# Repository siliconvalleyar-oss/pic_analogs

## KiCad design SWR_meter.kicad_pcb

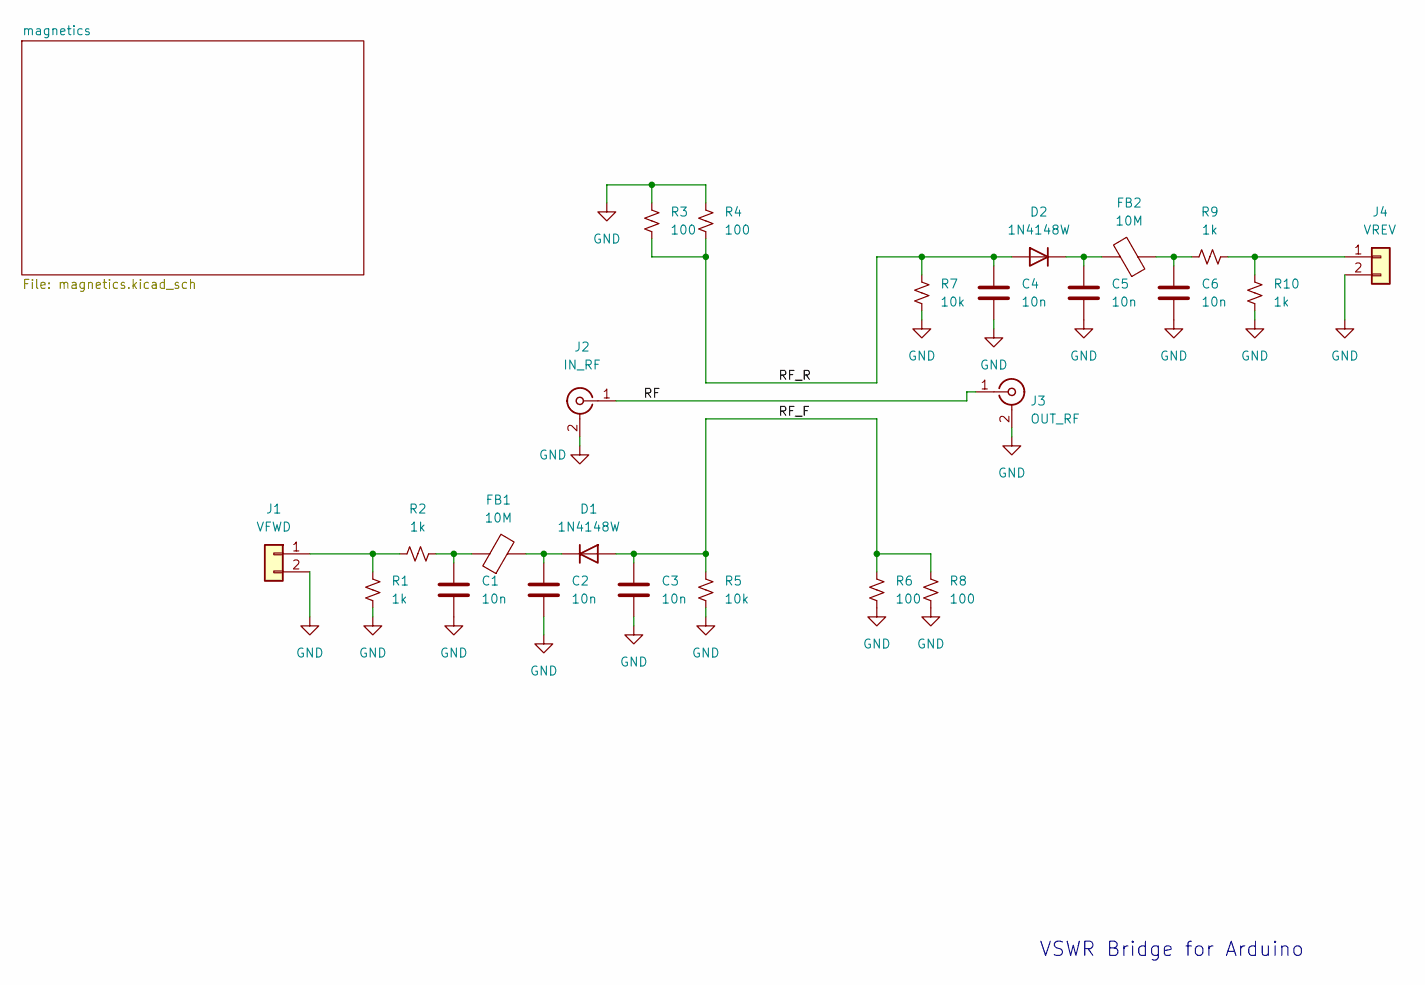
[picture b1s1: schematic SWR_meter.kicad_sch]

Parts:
C1, C2, C3, C4, C5, C6: 10n; C_0805_2012Metric
D1, D2: 1N4148W; D_SOD-123
FB1, FB2: 10M; L_1206_3216Metric
J1: VFWD; PinSocket_1x02_P2.54mm_Vertical
J2: IN_RF; SMA_Samtec_SMA-J-P-X-ST-EM1_EdgeMount
J3: OUT_RF; SMA_Samtec_SMA-J-P-X-ST-EM1_EdgeMount
J4: VREV; PinSocket_1x02_P2.54mm_Vertical
R1, R2, R9, R10: 1k; R_0805_2012Metric
R3, R4, R6, R8: 100; R_0805_2012Metric
R5, R7: 10k; R_0805_2012Metric

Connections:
/RF: J2.1 (In), J3.1 (In)
/RF_F: C3.1, D1.2 (A), R5.1, R6.1, R8.1
/RF_R: C4.1, D2.2 (A), R3.2, R4.2, R7.1
GND: C1.2, C2.2, C3.2, C4.2, C5.2, C6.2, J1.2, J2.2 (Ext), J3.2 (Ext), J4.2, R1.1, R3.1, R4.1, R5.2, R6.2, R7.2, R8.2, R10.1; also elsewhere on the board
unnamed: C1.1, FB1.1, R2.2
unnamed: C6.1, FB2.1, R9.1
unnamed: C2.1, D1.1 (K), FB1.2
unnamed: C5.1, D2.1 (K), FB2.2
unnamed: J1.1, R1.2, R2.1
unnamed: J4.1, R9.2, R10.2

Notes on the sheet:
VSWR Bridge for Arduino

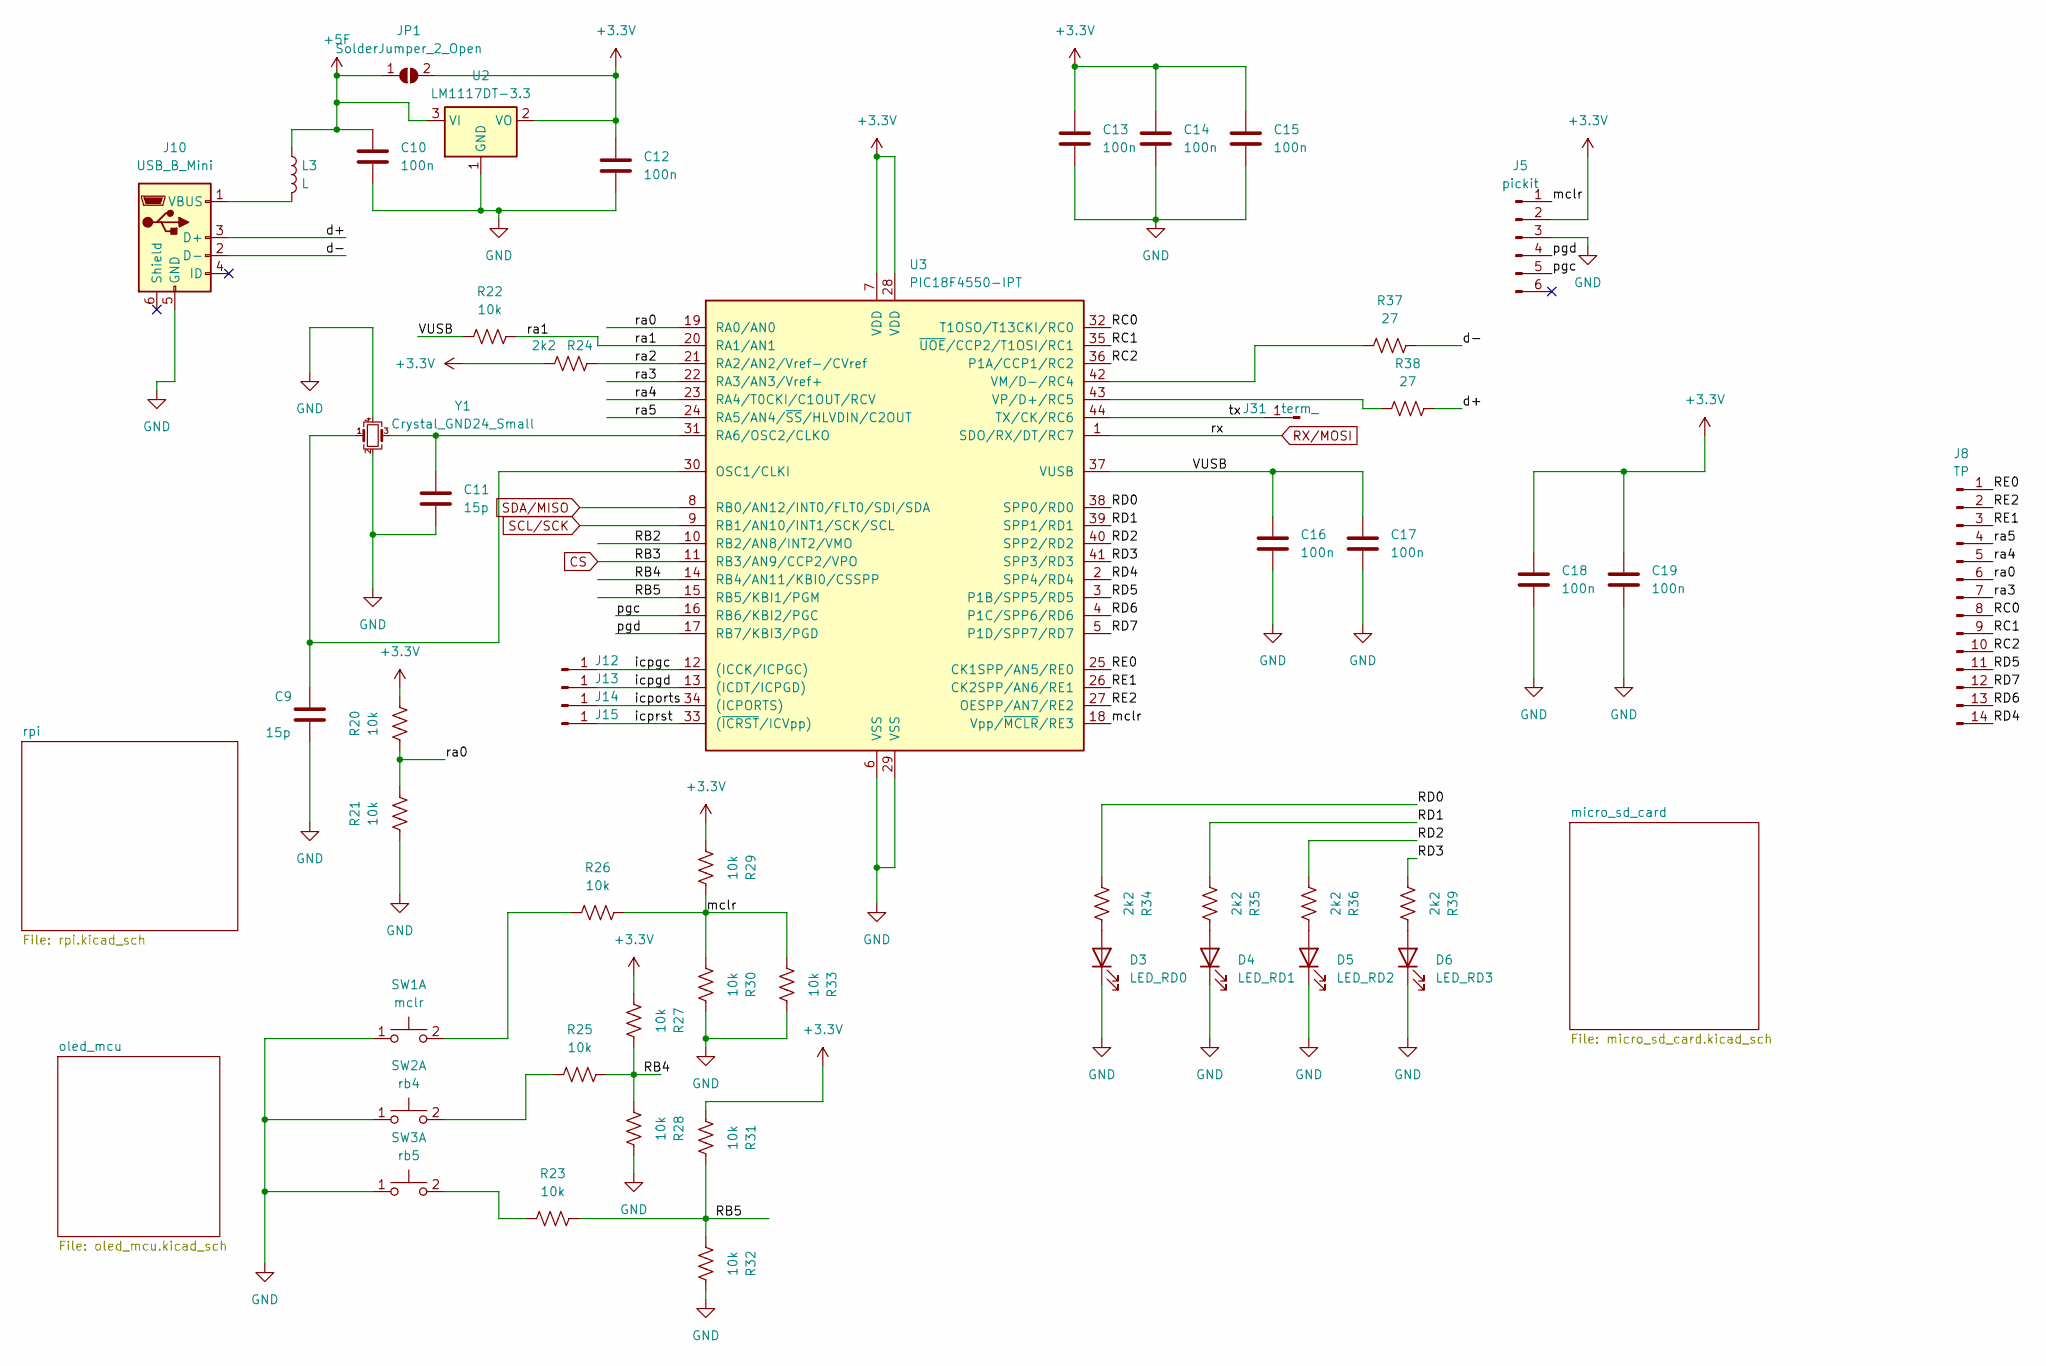
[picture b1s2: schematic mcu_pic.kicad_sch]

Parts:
C9, C11: 15p; C_0805_2012Metric
C10, C12: 100n; C_1206_3216Metric
C13, C14, C15, C16, C17, C18, C19: 100n; C_0603_1608Metric
D3: LED_RD0; D_0805_2012Metric
D4: LED_RD1; D_0805_2012Metric
D5: LED_RD2; D_0805_2012Metric
D6: LED_RD3; D_0805_2012Metric
J5: pickit; PinHeader_1x06_P2.54mm_Horizontal
J8: TP; PinHeader_2x08_P2.54mm_Vertical
J10: USB_B_Mini; USB_Mini-B_Wuerth_65100516121_Horizontal
J12, J13, J14, J15: connector_pin_smd_1mm
J31: term_; connector_pin_smd_1mm
JP1: SolderJumper_2_Open; SolderJumper-2_P1.3mm_Open_TrianglePad1.0x1.5mm
L3: L; L_Neosid_Ms42
R20, R21, R22, R23, R25, R26, R27, R28, R29, R30, R31, R32, R33: 10k; R_0603_1608Metric
R24, R34, R35, R36, R39: 2k2; R_0603_1608Metric
R37, R38: 27; R_0603_1608Metric
SW1: mclr; SW_Push_1P1T_NO_CK_KSC6xxJ
SW2: rb4; SW_Push_1P1T_NO_CK_KSC6xxJ
SW3: rb5; SW_Push_1P1T_NO_CK_KSC6xxJ
U2: LM1117DT-3.3; TO-252-3_TabPin2
U3: PIC18F4550-IPT; TQFP-44_10x10mm_P0.8mm
Y1: Crystal_GND24_Small; Oscillator_SMD_Abracon_ASE-4Pin_3.2x2.5mm

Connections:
+3.3V: C12.1, C13.1, C14.1, C15.1, C18.1, C19.1, J5.2, JP1.2 (B), R20.1, R24.2, R27.2, R29.2, R31.2, U2.2 (VO), U3.7 (VDD), U3.28 (VDD); also elsewhere on the board
+5F: C10.1, JP1.1 (A), L3.1, U2.3 (VI); also elsewhere on the board
/magnetics/mcu_pic/RB2: U3.10 (RB2/AN8/INT2/VMO)
/magnetics/mcu_pic/RB4: R25.1, R27.1, R28.2, U3.14 (RB4/AN11/KBI0/CSSPP)
/magnetics/mcu_pic/RB5: R23.1, R31.1, R32.2, U3.15 (RB5/KBI1/PGM)
/magnetics/mcu_pic/RC0: J8.8, U3.32 (T1OSO/T13CKI/RC0)
/magnetics/mcu_pic/RC1: J8.9, U3.35 (~UOE/CCP2/T1OSI/RC1)
/magnetics/mcu_pic/RC2: J8.10, U3.36 (P1A/CCP1/RC2)
/magnetics/mcu_pic/RD0: R34.2, U3.38 (SPP0/RD0)
/magnetics/mcu_pic/RD1: R35.2, U3.39 (SPP1/RD1)
/magnetics/mcu_pic/RD2: R36.2, U3.40 (SPP2/RD2)
/magnetics/mcu_pic/RD3: R39.2, U3.41 (SPP3/RD3)
/magnetics/mcu_pic/RD4: J8.14, U3.2 (SPP4/RD4)
/magnetics/mcu_pic/RD5: J8.11, U3.3 (P1B/SPP5/RD5)
/magnetics/mcu_pic/RD6: J8.13, U3.4 (P1C/SPP6/RD6)
/magnetics/mcu_pic/RD7: J8.12, U3.5 (P1D/SPP7/RD7)
/magnetics/mcu_pic/RE0: J8.1, U3.25 (CK1SPP/AN5/RE0)
/magnetics/mcu_pic/RE1: J8.3, U3.26 (CK2SPP/AN6/RE1)
/magnetics/mcu_pic/RE2: J8.2, U3.27 (OESPP/AN7/RE2)
/magnetics/mcu_pic/VUSB: C16.1, C17.1, R22.2, U3.37 (VUSB)
/magnetics/mcu_pic/d+: J10.3 (D+), R38.1
/magnetics/mcu_pic/d-: J10.2 (D-), R37.1
/magnetics/mcu_pic/icpgc: J12.1 (Pin_1_1), U3.12 ((ICCK/ICPGC))
/magnetics/mcu_pic/icpgd: J13.1 (Pin_1_1), U3.13 ((ICDT/ICPGD))
/magnetics/mcu_pic/icports: J14.1 (Pin_1_1), U3.34 ((ICPORTS))
/magnetics/mcu_pic/icprst: J15.1 (Pin_1_1), U3.33 ((~ICRST/ICVpp))
/magnetics/mcu_pic/mclr: J5.1, R26.1, R29.1, R30.2, R33.2, U3.18 (Vpp/~MCLR/RE3)
/magnetics/mcu_pic/pgc: J5.5, U3.16 (RB6/KBI2/PGC)
/magnetics/mcu_pic/pgd: J5.4, U3.17 (RB7/KBI3/PGD)
/magnetics/mcu_pic/ra0: J8.6, R20.2, R21.1, U3.19 (RA0/AN0)
/magnetics/mcu_pic/ra1: R22.1, U3.20 (RA1/AN1)
/magnetics/mcu_pic/ra2: R24.1, U3.21 (RA2/AN2/Vref-/CVref)
/magnetics/mcu_pic/ra3: J8.7, U3.22 (RA3/AN3/Vref+)
/magnetics/mcu_pic/ra4: J8.5, U3.23 (RA4/T0CKI/C1OUT/RCV)
/magnetics/mcu_pic/ra5: J8.4, U3.24 (RA5/AN4/~SS/HLVDIN/C2OUT)
/magnetics/mcu_pic/tx: J31.1 (Pin_1_1), U3.44 (TX/CK/RC6)
CS: U3.11 (RB3/AN9/CCP2/VPO); also elsewhere on the board
GND: C9.2, C10.2, C11.2, C12.2, C13.2, C14.2, C15.2, C16.2, C17.2, C18.2, C19.2, D3.1 (K), D4.1 (K), D5.1 (K), D6.1 (K), J5.3, J10.5 (GND), J10.6 (Shield), R21.2, R28.1, R30.1, R32.1, R33.1, SW1.1 (C), SW2.1 (C), SW3.1 (C), U2.1 (GND), U3.6 (VSS), U3.29 (VSS), Y1.2, Y1.4; also elsewhere on the board
unnamed: D3.2 (A), R34.1
unnamed: D4.2 (A), R35.1
unnamed: D5.2 (A), R36.1
unnamed: D6.2 (A), R39.1
unnamed: J10.1 (VBUS), L3.2
unnamed: R26.2, SW1.2 (D)
unnamed: R25.2, SW2.2 (D)
unnamed: R23.2, SW3.2 (D)
unnamed: C9.1, U3.30 (OSC1/CLKI), Y1.1
unnamed: C11.1, U3.31 (RA6/OSC2/CLKO), Y1.3
unnamed: R37.2, U3.42 (VM/D-/RC4)
unnamed: R38.2, U3.43 (VP/D+/RC5)
RX/MOSI: U3.1 (SDO/RX/DT/RC7); also elsewhere on the board
SCL/SCK: U3.9 (RB1/AN10/INT1/SCK/SCL); also elsewhere on the board
SDA/MISO: U3.8 (RB0/AN12/INT0/FLT0/SDI/SDA); also elsewhere on the board

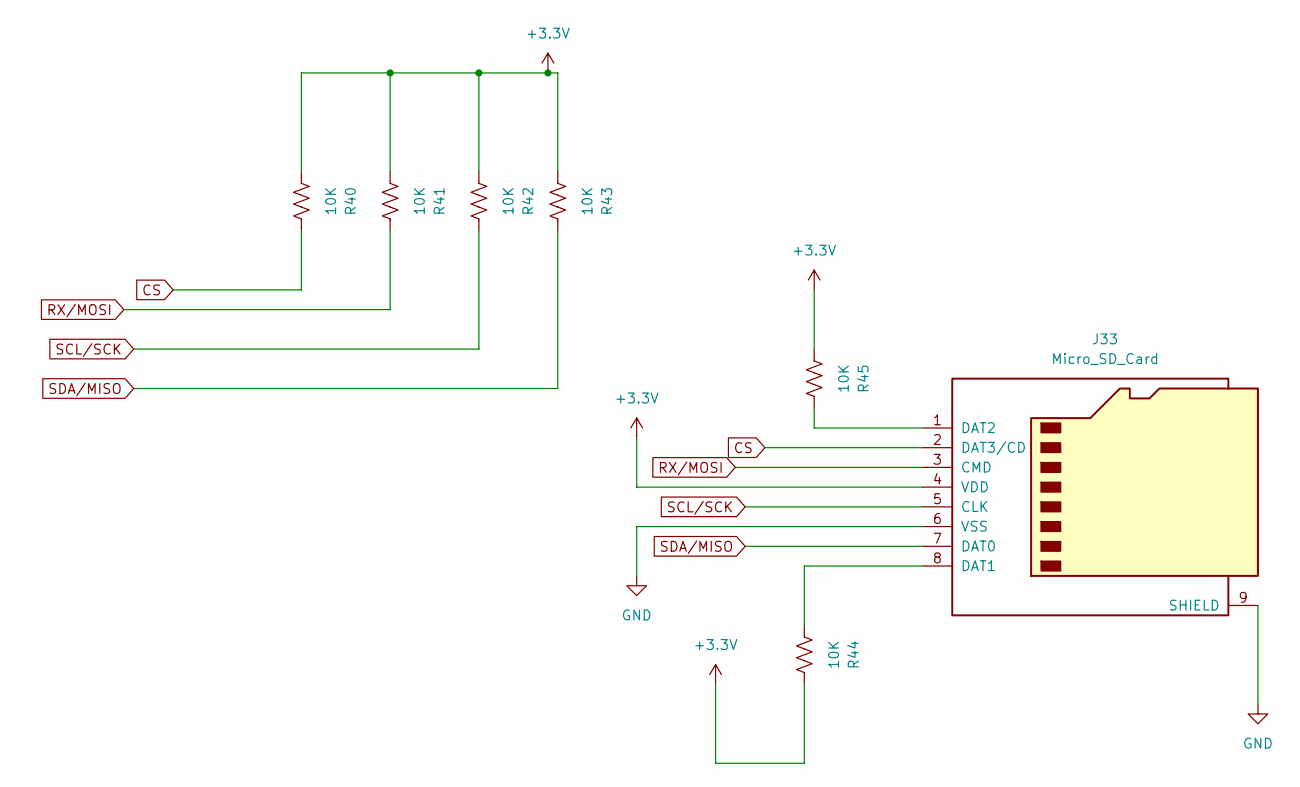
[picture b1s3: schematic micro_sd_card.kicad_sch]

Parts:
J33: Micro_SD_Card; 3M_2908-05WB-MG
R40, R41, R42, R43, R44, R45: 10K; R_0603_1608Metric

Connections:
+3.3V: J33.4 (VDD), R40.2, R41.2, R42.2, R43.2, R44.1, R45.2; also elsewhere on the board
CS: J33.2 (DAT3/CD), R40.1; also elsewhere on the board
GND: J33.6 (VSS), J33.9 (SHIELD); also elsewhere on the board
unnamed: J33.8 (DAT1), R44.2
unnamed: J33.1 (DAT2), R45.1
RX/MOSI: J33.3 (CMD), R41.1; also elsewhere on the board
SCL/SCK: J33.5 (CLK), R42.1; also elsewhere on the board
SDA/MISO: J33.7 (DAT0), R43.1; also elsewhere on the board

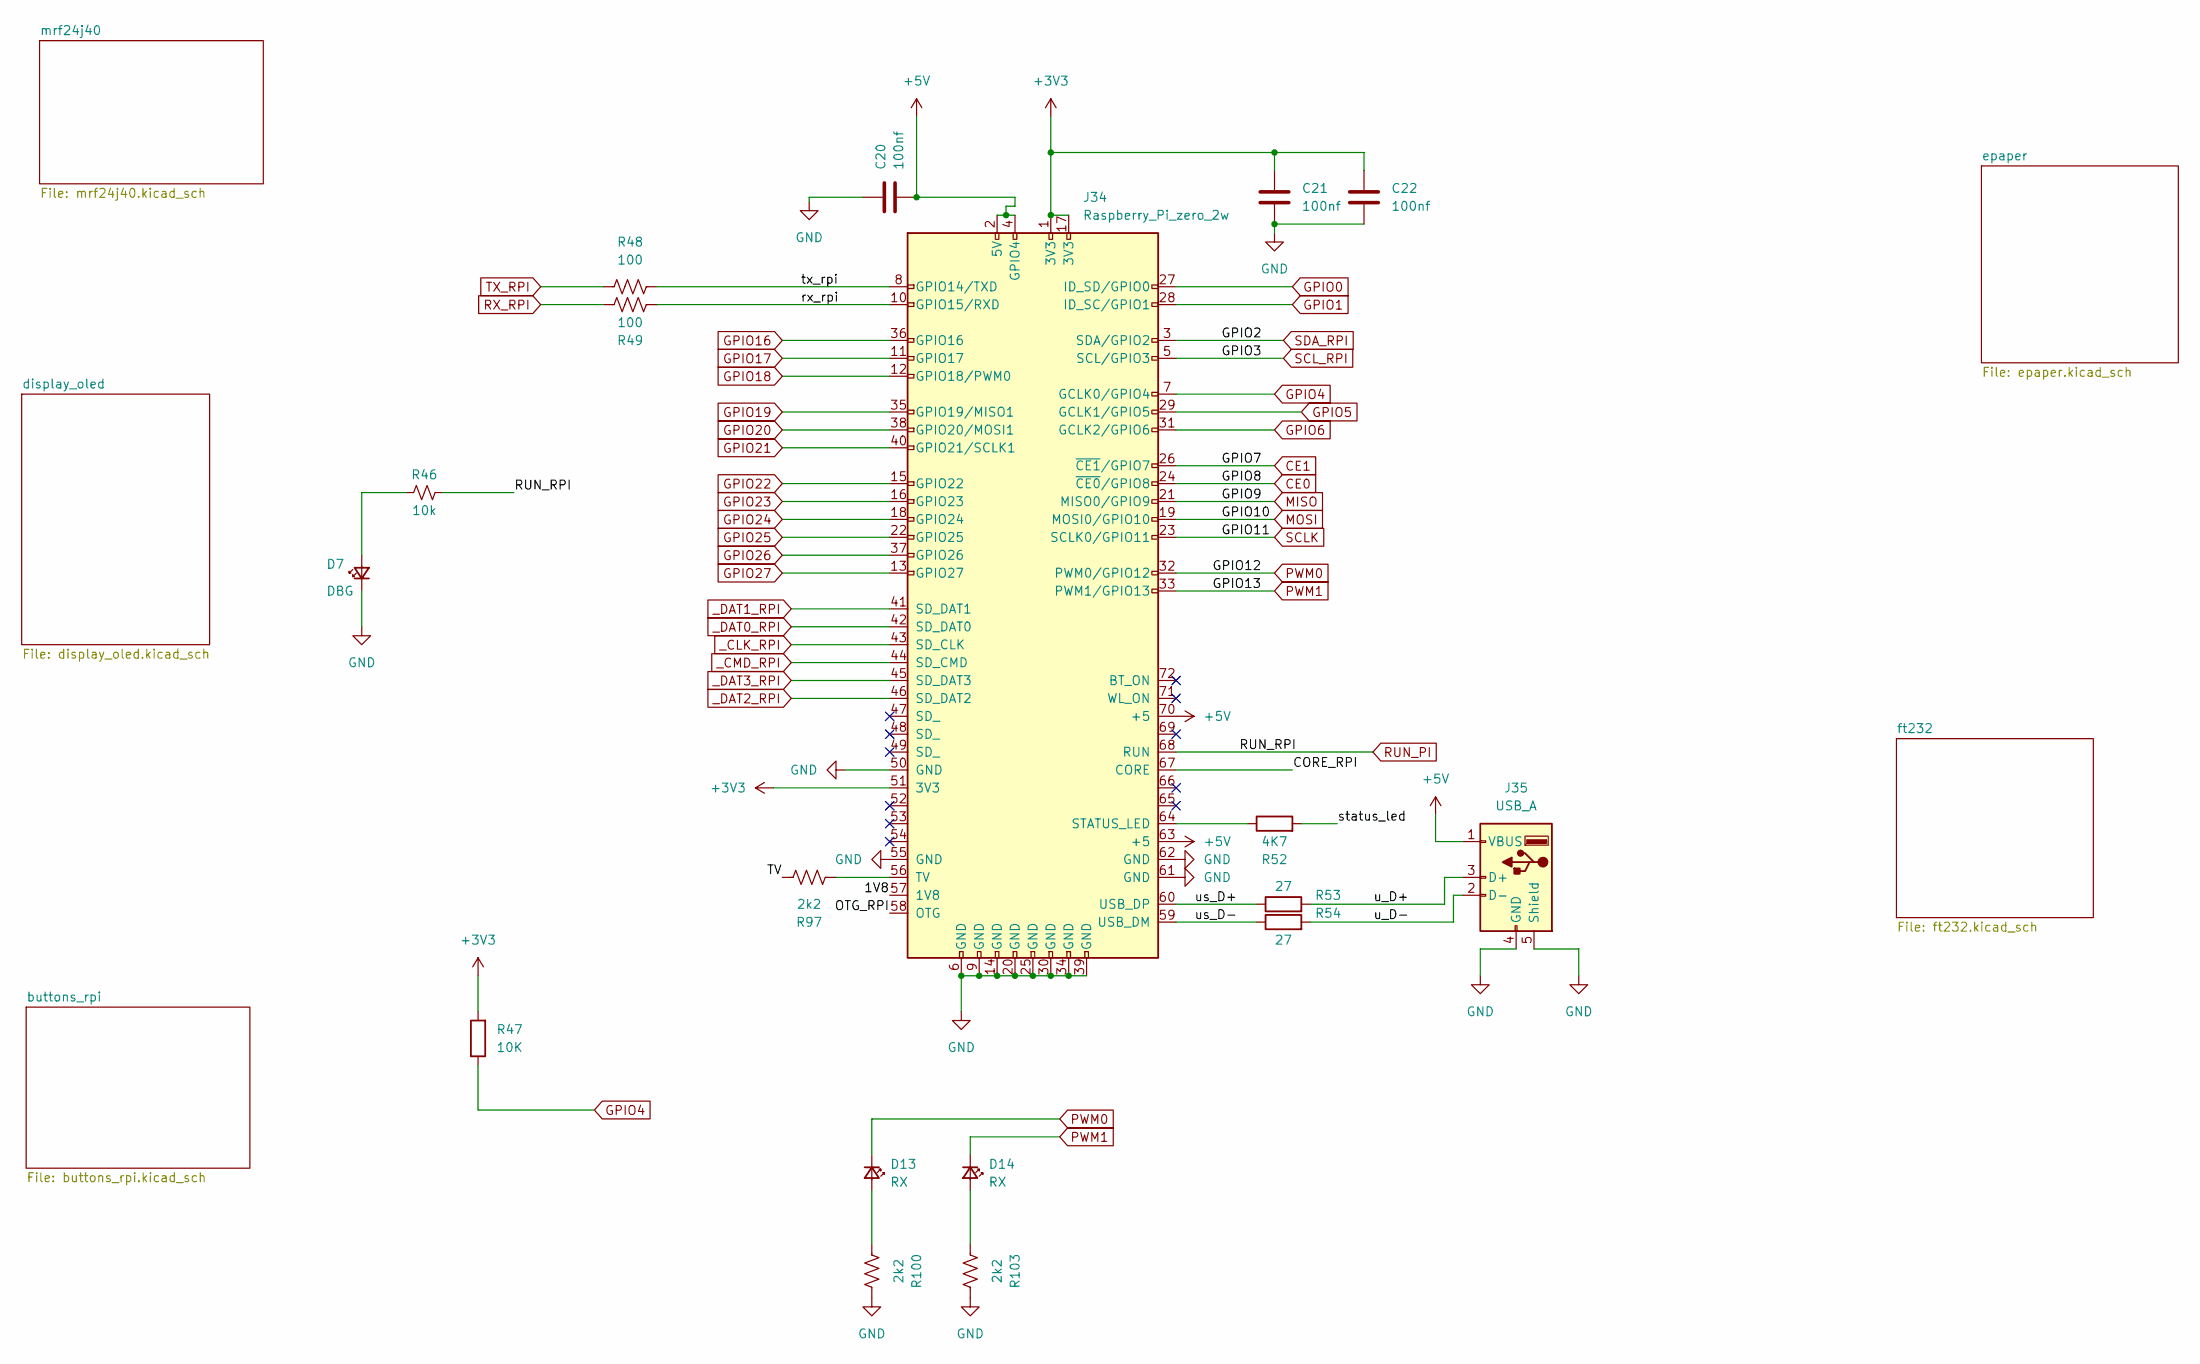
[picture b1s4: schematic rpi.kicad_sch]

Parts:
C20: 100nf; C_0805_2012Metric
C21, C22: 100nf; C_0603_1608Metric
D7: DBG; LED_0805_2012Metric
D13, D14: RX; D_0805_2012Metric
J34: Raspberry_Pi_zero_2w; Raspberry_Pi_Zero_2w_top_rpi
J35: USB_A; USB_A_CONNFLY_DS1095-WNR0_V2
R46: 10k; R_0603_1608Metric
R47: 10K; R_0603_1608Metric
R48, R49: 100; R_0603_1608Metric
R52: 4K7; R_0603_1608Metric
R53, R54: 27; R_0603_1608Metric
R97: 2k2; R_0603_1608Metric
R100, R103: 2k2; R_0805_2012Metric

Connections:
+3V3: C21.1, C22.1, J34.1 (3V3), J34.17 (3V3), J34.51 (3V3), R47.2; also elsewhere on the board
+5V: C20.2, J34.2 (5V), J34.4 (GPIO4), J34.63 (+5), J34.70 (+5), J35.1 (VBUS); also elsewhere on the board
/magnetics/mcu_pic/rpi/1V8: J34.57 (1V8)
/magnetics/mcu_pic/rpi/CORE_RPI: J34.67 (CORE)
/magnetics/mcu_pic/rpi/OTG_RPI: J34.58 (OTG)
/magnetics/mcu_pic/rpi/TV: R97.1
/magnetics/mcu_pic/rpi/rx_rpi: J34.10 (GPIO15/RXD), R49.1
/magnetics/mcu_pic/rpi/status_led: R52.2
/magnetics/mcu_pic/rpi/tx_rpi: J34.8 (GPIO14/TXD), R48.1
/magnetics/mcu_pic/rpi/u_D+: J35.3 (D+), R53.2
/magnetics/mcu_pic/rpi/u_D-: J35.2 (D-), R54.2
/magnetics/mcu_pic/rpi/us_D+: J34.60 (USB_DP), R53.1
/magnetics/mcu_pic/rpi/us_D-: J34.59 (USB_DM), R54.1
CE0: J34.24 (~CE0/GPIO8); also elsewhere on the board
CE1: J34.26 (~CE1/GPIO7); also elsewhere on the board
CSB: J34.16 (GPIO23); also elsewhere on the board
GND: C20.1, C21.2, C22.2, D7.1 (K), J34.6 (GND), J34.9 (GND), J34.14 (GND), J34.20 (GND), J34.25 (GND), J34.30 (GND), J34.34 (GND), J34.39 (GND), J34.50 (GND), J34.55 (GND), J34.61 (GND), J34.62 (GND), J35.4 (GND), J35.5 (Shield), R100.1, R103.1; also elsewhere on the board
GPIO0: J34.27 (ID_SD/GPIO0); also elsewhere on the board
GPIO1: J34.28 (ID_SC/GPIO1); also elsewhere on the board
GPIO4: J34.7 (GCLK0/GPIO4), R47.1
GPIO5: J34.29 (GCLK1/GPIO5); also elsewhere on the board
GPIO6: J34.31 (GCLK2/GPIO6); also elsewhere on the board
GPIO16: J34.36 (GPIO16)
GPIO17: J34.11 (GPIO17); also elsewhere on the board
GPIO18: J34.12 (GPIO18/PWM0); also elsewhere on the board
GPIO19: J34.35 (GPIO19/MISO1); also elsewhere on the board
GPIO20: J34.38 (GPIO20/MOSI1)
GPIO21: J34.40 (GPIO21/SCLK1)
GPIO22: J34.15 (GPIO22); also elsewhere on the board
GPIO24: J34.18 (GPIO24); also elsewhere on the board
GPIO25: J34.22 (GPIO25); also elsewhere on the board
GPIO26: J34.37 (GPIO26); also elsewhere on the board
GPIO27: J34.13 (GPIO27); also elsewhere on the board
MISO: J34.21 (MISO0/GPIO9); also elsewhere on the board
MOSI: J34.19 (MOSI0/GPIO10); also elsewhere on the board
unnamed: D7.2 (A), R46.1
unnamed: D13.2 (A), R100.2
unnamed: D14.2 (A), R103.2
unnamed: J34.64 (STATUS_LED), R52.1
unnamed: J34.56 (TV), R97.2
PWM0: D13.1 (K), J34.32 (PWM0/GPIO12)
PWM1: D14.1 (K), J34.33 (PWM1/GPIO13)
RUN_PI: J34.68 (RUN), R46.2; also elsewhere on the board
RX_RPI: R49.2; also elsewhere on the board
SCLK: J34.23 (SCLK0/GPIO11); also elsewhere on the board
SCL_RPI: J34.5 (SCL/GPIO3)
SDA_RPI: J34.3 (SDA/GPIO2)
TX_RPI: R48.2; also elsewhere on the board
_CLK_RPI: J34.43 (SD_CLK)
_CMD_RPI: J34.44 (SD_CMD)
_DAT0_RPI: J34.42 (SD_DAT0)
_DAT1_RPI: J34.41 (SD_DAT1)
_DAT2_RPI: J34.46 (SD_DAT2)
_DAT3_RPI: J34.45 (SD_DAT3)

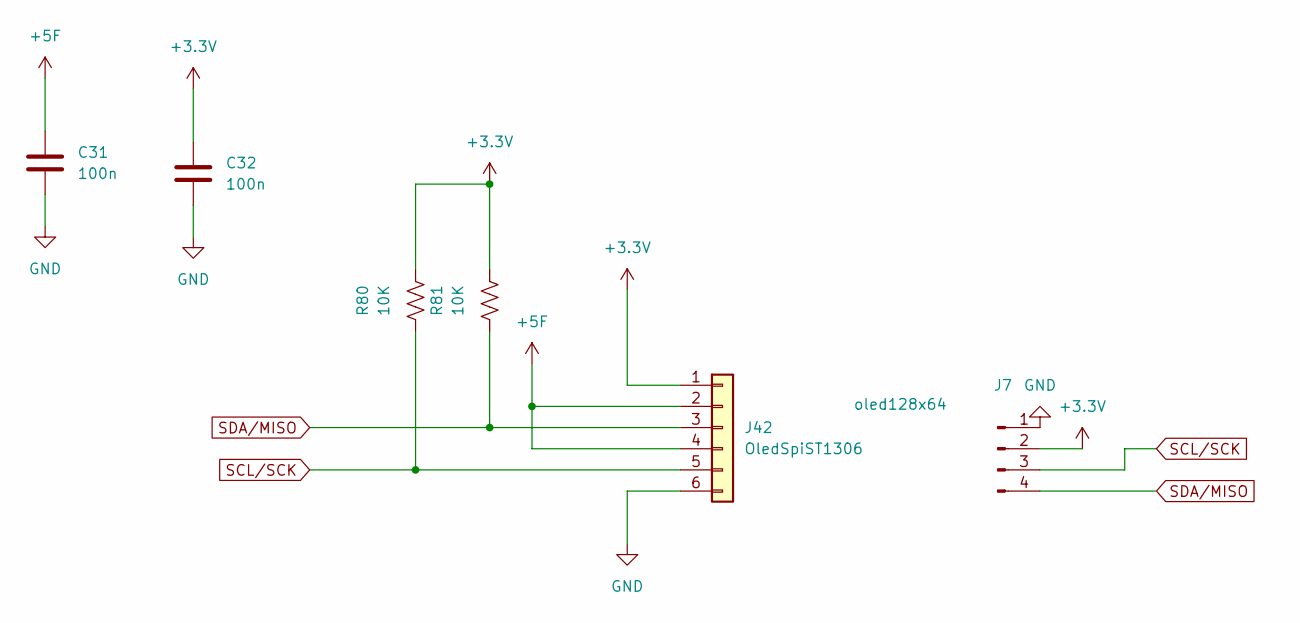
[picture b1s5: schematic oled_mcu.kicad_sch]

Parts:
C31, C32: 100n; C_0603_1608Metric
J7: oled128x64; SSD1306_No_Mounting_whitout_Holes
J42: OledSpiST1306; PinHeader_2x03_P2.54mm_Vertical
R80, R81: 10K; R_0603_1608Metric

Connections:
+3.3V: C32.1, J7.2, J42.1, R80.1, R81.1; also elsewhere on the board
+5F: C31.1, J42.2, J42.4; also elsewhere on the board
GND: C31.2, C32.2, J7.1, J42.6; also elsewhere on the board
SCL/SCK: J7.3, J42.5, R80.2; also elsewhere on the board
SDA/MISO: J7.4, J42.3, R81.2; also elsewhere on the board

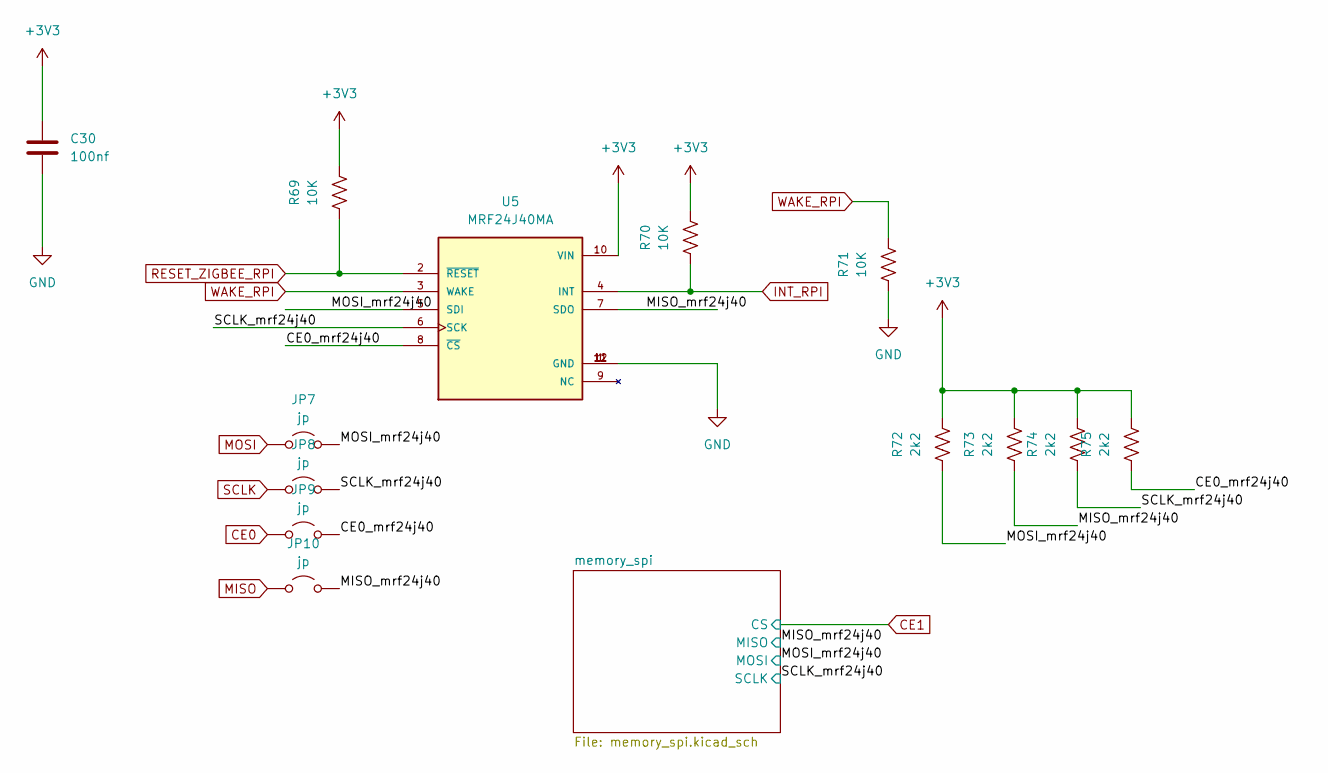
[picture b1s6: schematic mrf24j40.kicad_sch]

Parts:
C30: 100nf; C_0603_1608Metric
JP7, JP8, JP9, JP10: jp; SolderJumper-2_P1.3mm_Open_RoundedPad1.0x1.5mm
R69, R70, R71: 10K; R_0805_2012Metric
R72, R73, R74, R75: 2k2; R_0805_2012Metric
U5: MRF24J40MA; MODULE_MRF24J40MA; PARTREV 05/14/19

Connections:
+3V3: C30.1, R69.1, R70.1, R72.1, R73.1, R74.1, R75.1, U5.10 (VIN); also elsewhere on the board
/magnetics/mcu_pic/rpi/mrf24j40/CE0_mrf24j40: JP9.2 (B), R75.2, U5.8 (~CS)
/magnetics/mcu_pic/rpi/mrf24j40/MISO_mrf24j40: JP10.2 (B), R73.2, U5.7 (SDO); also elsewhere on the board
/magnetics/mcu_pic/rpi/mrf24j40/MOSI_mrf24j40: JP7.2 (B), R72.2, U5.5 (SDI); also elsewhere on the board
/magnetics/mcu_pic/rpi/mrf24j40/SCLK_mrf24j40: JP8.2 (B), R74.2, U5.6 (SCK); also elsewhere on the board
CE0: JP9.1 (A); also elsewhere on the board
GND: C30.2, R71.2, U5.1 (GND), U5.11 (GND), U5.12 (GND); also elsewhere on the board
INT_RPI: R70.2, U5.4 (INT)
MISO: JP10.1 (A); also elsewhere on the board
MOSI: JP7.1 (A); also elsewhere on the board
RESET_ZIGBEE_RPI: R69.2, U5.2 (~RESET)
SCLK: JP8.1 (A); also elsewhere on the board
WAKE_RPI: R71.1, U5.3 (WAKE)

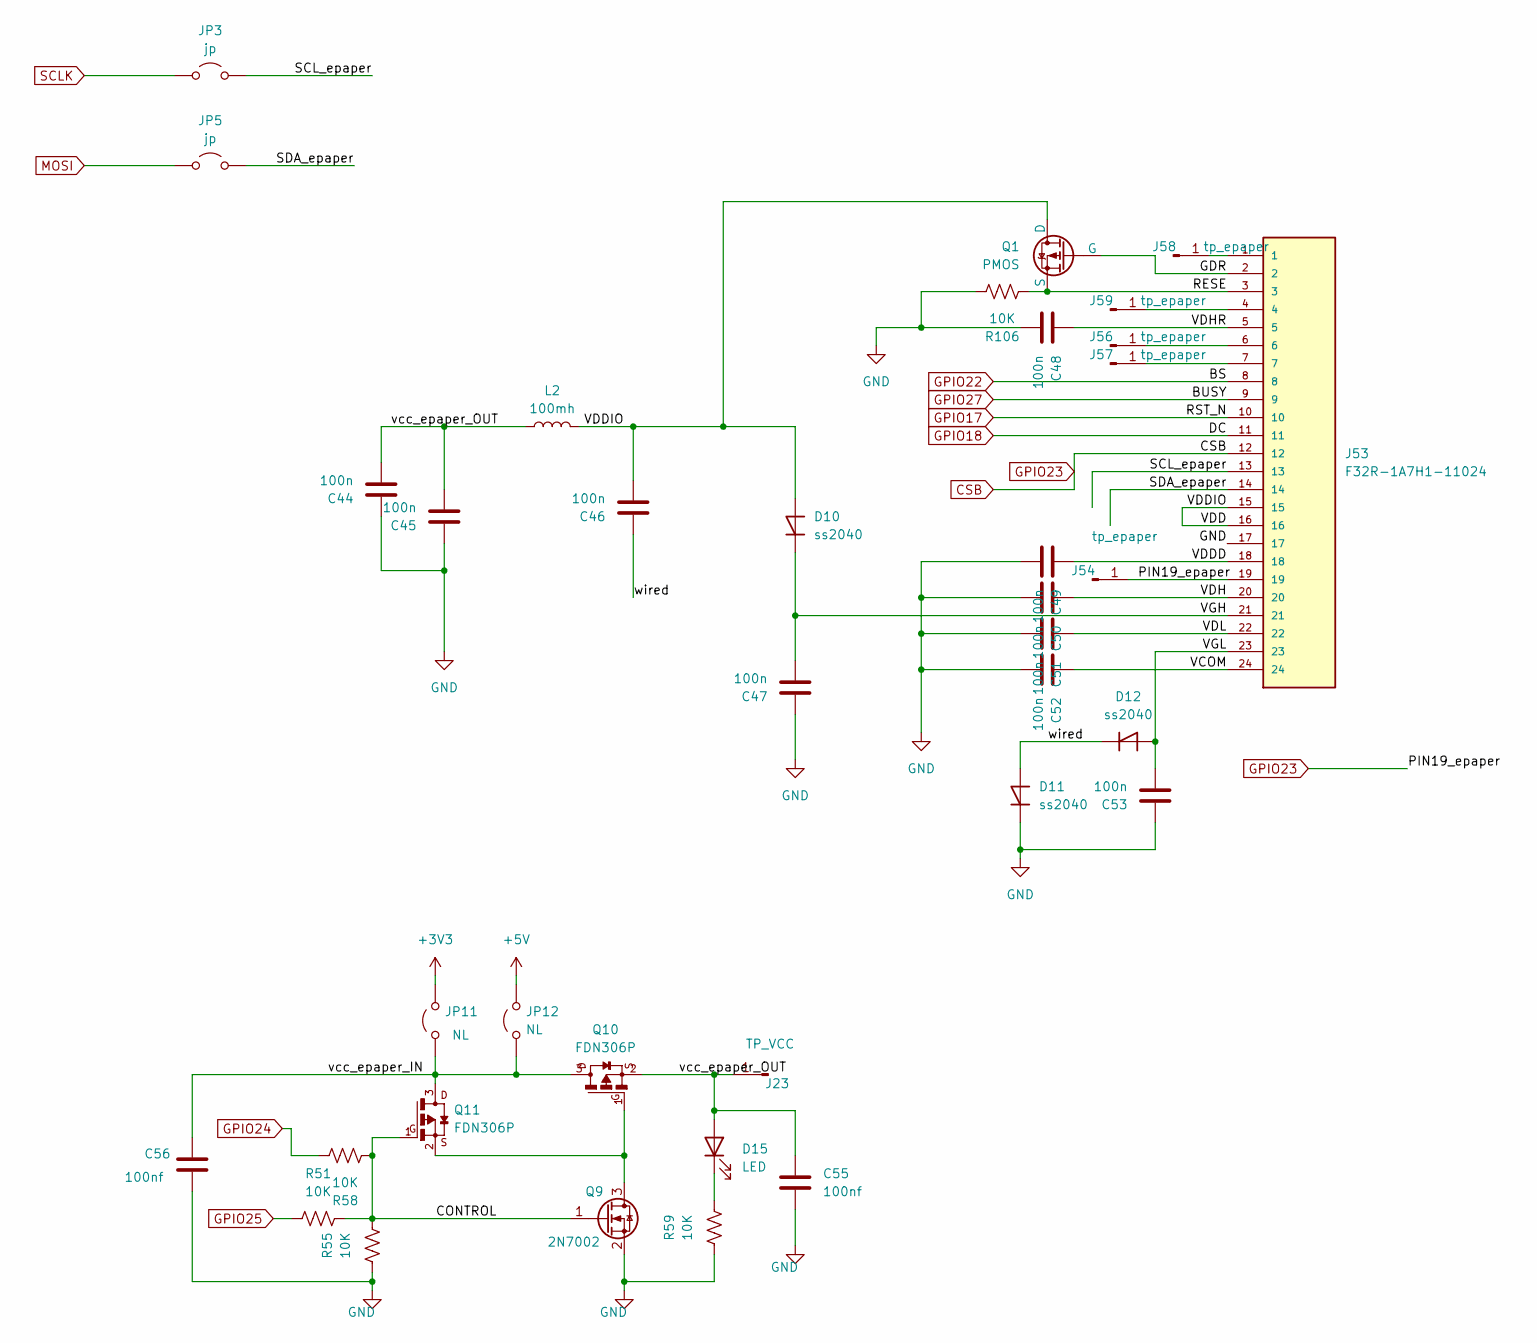
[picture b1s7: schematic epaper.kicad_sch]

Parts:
C44, C45, C46, C47: 100n; C_0805_2012Metric
C48, C49, C50, C51, C52, C53: 100n; C_0603_1608Metric
C55, C56: 100nf; C_0805_2012Metric
D10, D11, D12: ss2040; D_SOD-128
D15: LED; D_0805_2012Metric
J23: TP_VCC; TestPoint_THTPad_1.0x1.0mm_Drill0.5mm
J53: F32R-1A7H1-11024; AMPHENOL_F32R-1A7H1-11024; PARTREV C
J54, J56, J57, J58, J59: tp_epaper; TestPoint_Pad_1.0x1.0mm
JP3, JP5: jp; SolderJumper-2_P1.3mm_Open_RoundedPad1.0x1.5mm
JP11, JP12: NL; SolderJumper-2_P1.3mm_Open_RoundedPad1.0x1.5mm
L2: 100mh; L_6.3x6.3_H3
Q1: PMOS; SOT-323_SC-70
Q9: 2N7002; SOT-23
Q10, Q11: FDN306P; SOT-23W
R51, R55, R58, R59: 10K; R_0805_2012Metric
R106: 10K; R_0603_1608Metric

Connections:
+3V3: JP11.2 (B); also elsewhere on the board
+5V: JP12.2 (B); also elsewhere on the board
/magnetics/mcu_pic/rpi/epaper/CONTROL: Q9.1 (G), Q11.1, R51.1, R55.1, R58.2
/magnetics/mcu_pic/rpi/epaper/GDR: J53.2, Q1.2 (G)
/magnetics/mcu_pic/rpi/epaper/RESE: J53.3, Q1.3 (S), R106.2
/magnetics/mcu_pic/rpi/epaper/SCL_epaper: J53.13, JP3.2 (B)
/magnetics/mcu_pic/rpi/epaper/SDA_epaper: J53.14, JP5.2 (B)
/magnetics/mcu_pic/rpi/epaper/VCOM: C52.1, J53.24
/magnetics/mcu_pic/rpi/epaper/VDD: C46.2, D10.2 (A), J53.15, J53.16, L2.2, Q1.1 (D)
/magnetics/mcu_pic/rpi/epaper/VDDD: C49.1, J53.18
/magnetics/mcu_pic/rpi/epaper/VDH: C50.1, J53.20
/magnetics/mcu_pic/rpi/epaper/VDHR: C48.1, J53.5
/magnetics/mcu_pic/rpi/epaper/VDL: C51.1, J53.22
/magnetics/mcu_pic/rpi/epaper/VGH: C47.2, D10.1 (K), J53.21
/magnetics/mcu_pic/rpi/epaper/VGL: C53.2, D12.2 (A), J53.23
/magnetics/mcu_pic/rpi/epaper/vcc_epaper_IN: C56.1, JP11.1 (A), JP12.1 (A), Q10.3, Q11.3
/magnetics/mcu_pic/rpi/epaper/vcc_epaper_OUT: C44.2, C45.2, C55.1, D15.2 (A), J23.1 (Pin_1_1), L2.1, Q10.2
/magnetics/mcu_pic/rpi/epaper/wired: C46.1, D11.2 (A), D12.1 (K)
CSB: J53.12, J53.19, J54.1 (Pin_1_1); also elsewhere on the board
GND: C44.1, C45.1, C47.1, C48.2, C49.2, C50.2, C51.2, C52.2, C53.1, C55.2, C56.2, D11.1 (K), J53.17, Q9.2 (S), R55.2, R59.2, R106.1; also elsewhere on the board
GPIO17: J53.10; also elsewhere on the board
GPIO18: J53.11; also elsewhere on the board
GPIO22: J53.8; also elsewhere on the board
GPIO24: R58.1; also elsewhere on the board
GPIO25: R51.2; also elsewhere on the board
GPIO27: J53.9; also elsewhere on the board
MOSI: JP5.1 (A); also elsewhere on the board
unnamed: D15.1 (K), R59.1
unnamed: J53.6, J56.1 (Pin_1_1)
unnamed: J53.7, J57.1 (Pin_1_1)
unnamed: J53.1, J58.1 (Pin_1_1)
unnamed: J53.4, J59.1 (Pin_1_1)
unnamed: Q9.3 (D), Q10.1, Q11.2
SCLK: JP3.1 (A); also elsewhere on the board
